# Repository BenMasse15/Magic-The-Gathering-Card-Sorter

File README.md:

TO DO:

- Assembly
- Adapt Motor Code for traditionnal sorting
- Make "Mana Shuffle" option

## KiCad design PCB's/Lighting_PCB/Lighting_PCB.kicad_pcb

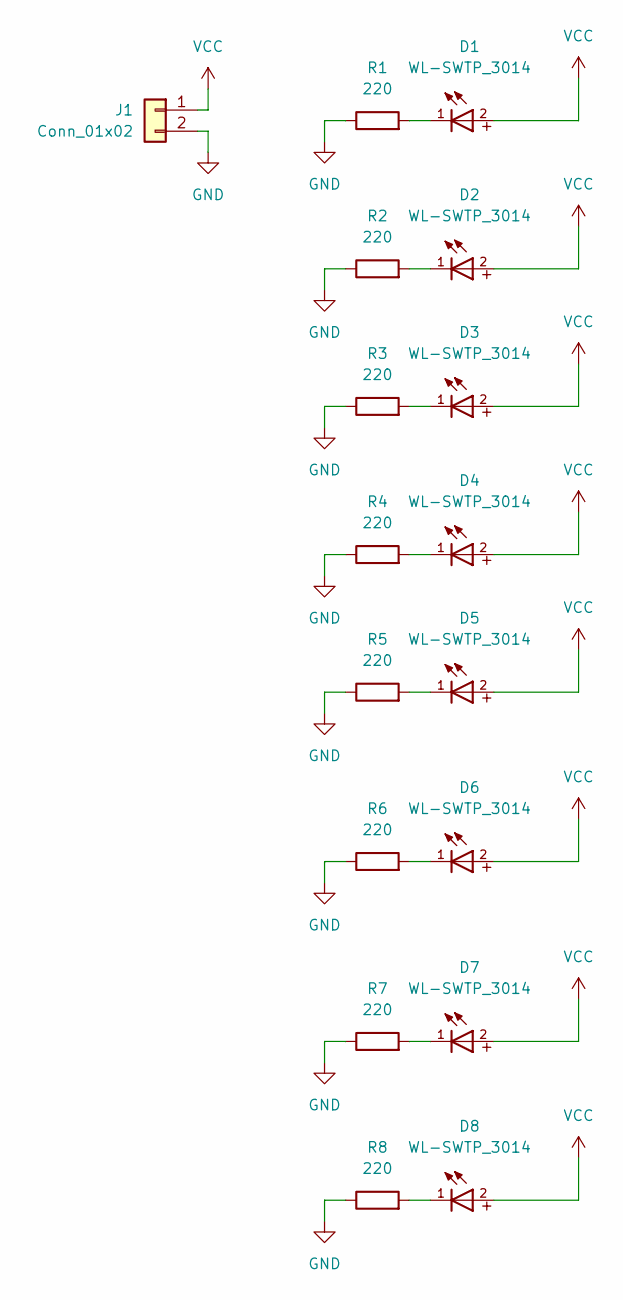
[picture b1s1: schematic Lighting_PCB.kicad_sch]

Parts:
D1, D2, D3, D4, D5, D6, D7, D8: WL-SWTP_3014
J1: Conn_01x02; Molex_KK-254_AE-6410-02A_1x02_P2.54mm_Vertical
R1, R2, R3, R4, R5, R6, R7, R8: 220; R_0805_2012Metric_Pad1.20x1.40mm_HandSolder

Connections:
GND: J1.2, R1.1, R2.1, R3.1, R4.1, R5.1, R6.1, R7.1, R8.1
unnamed: D1.1, R1.2
unnamed: D2.1, R2.2
unnamed: D3.1, R3.2
unnamed: D4.1, R4.2
unnamed: D5.1, R5.2
unnamed: D6.1, R6.2
unnamed: D7.1, R7.2
unnamed: D8.1, R8.2
VCC: D1.2, D2.2, D3.2, D4.2, D5.2, D6.2, D7.2, D8.2, J1.1

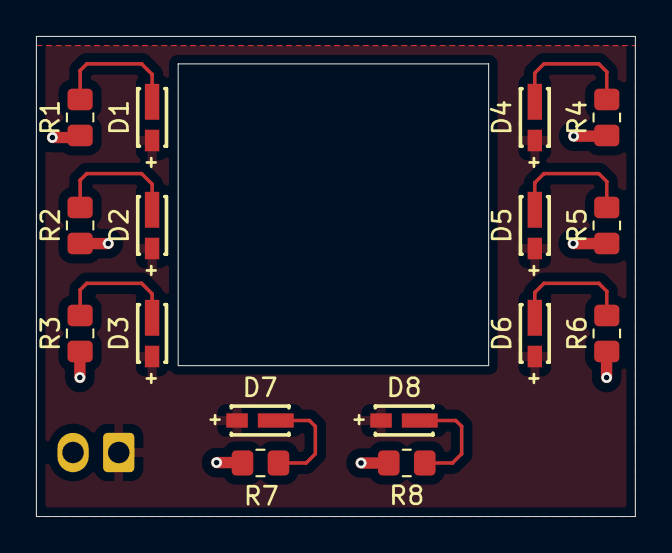
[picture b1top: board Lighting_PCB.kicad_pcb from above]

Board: 2 copper layers, 33.3 x 26.7 mm, 17 parts (1 on the bottom side), 10 nets.

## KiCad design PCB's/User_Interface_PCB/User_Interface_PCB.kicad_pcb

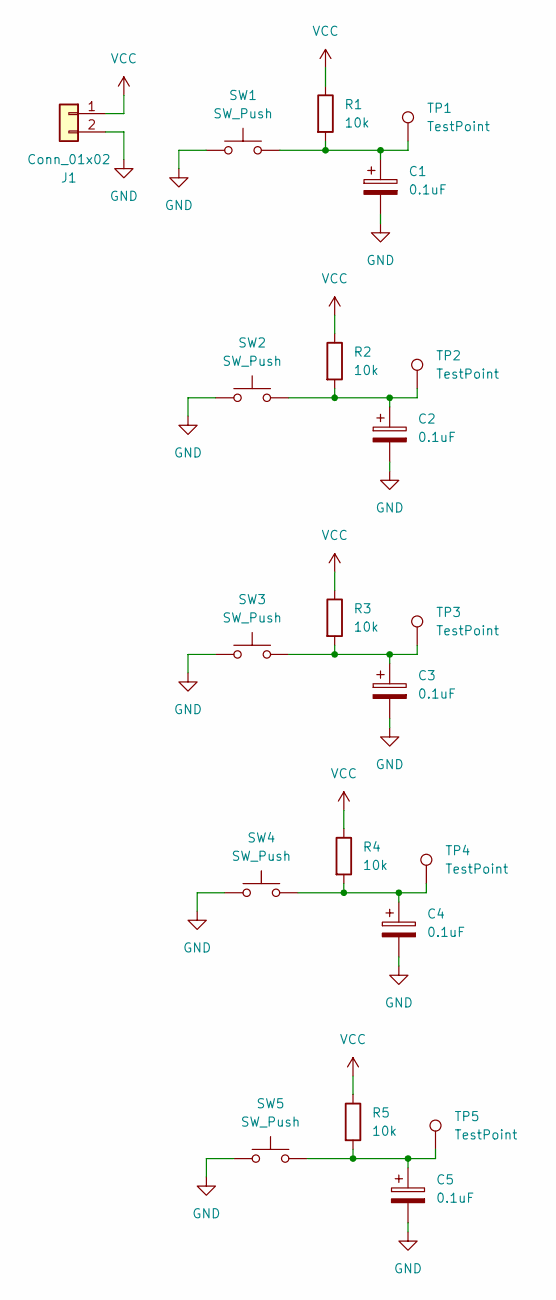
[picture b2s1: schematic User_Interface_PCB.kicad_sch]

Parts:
C1, C2, C3, C4, C5: 0.1uF; C_0805_2012Metric_Pad1.18x1.45mm_HandSolder
J1: Conn_01x02; Molex_KK-254_AE-6410-02A_1x02_P2.54mm_Vertical
R1, R2, R3, R4, R5: 10k; R_0805_2012Metric_Pad1.20x1.40mm_HandSolder
SW1, SW2, SW3, SW4, SW5: SW_Push; SW_MEC_5GTH9
TP1, TP2, TP3, TP4, TP5: TestPoint; TestPoint_Plated_Hole_D2.0mm

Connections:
GND: C1.2, C2.2, C3.2, C4.2, C5.2, J1.2, SW1.1, SW2.1, SW3.1, SW4.1, SW5.1
unnamed: C1.1, R1.2, SW1.2, TP1.1
unnamed: C2.1, R2.2, SW2.2, TP2.1
unnamed: C3.1, R3.2, SW3.2, TP3.1
unnamed: C4.1, R4.2, SW4.2, TP4.1
unnamed: C5.1, R5.2, SW5.2, TP5.1
VCC: J1.1, R1.1, R2.1, R3.1, R4.1, R5.1

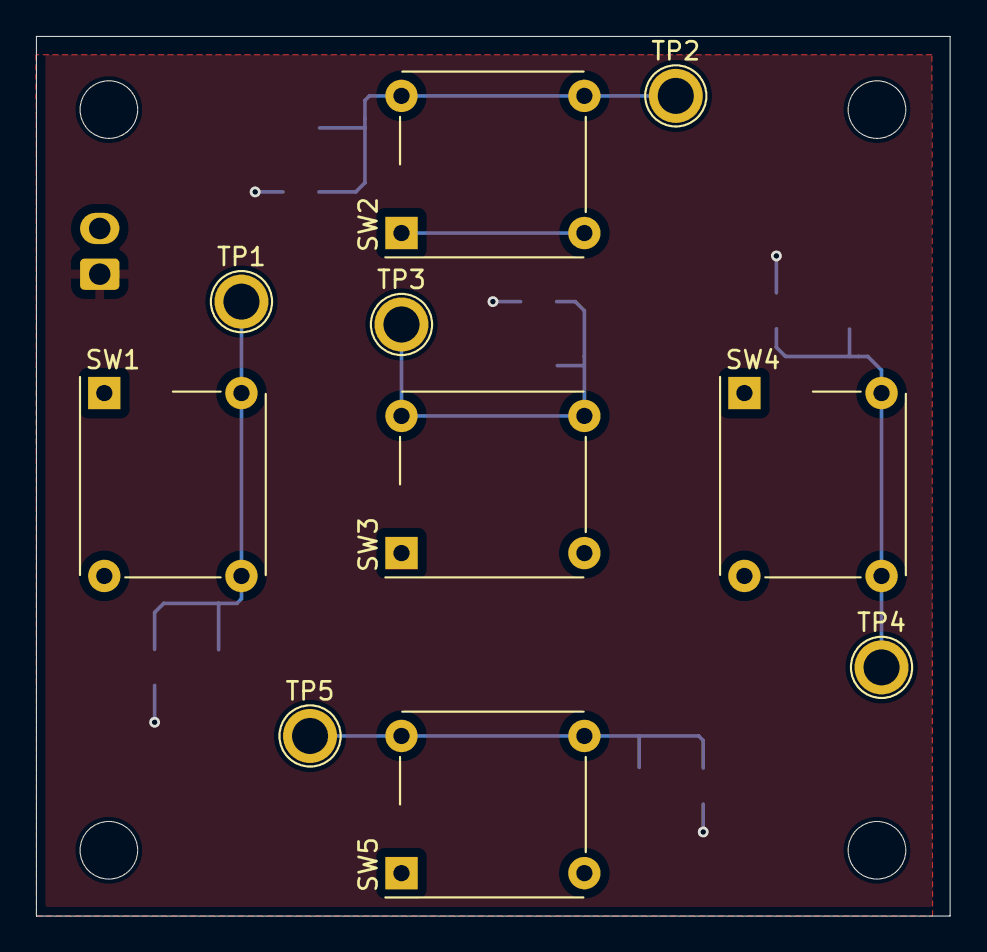
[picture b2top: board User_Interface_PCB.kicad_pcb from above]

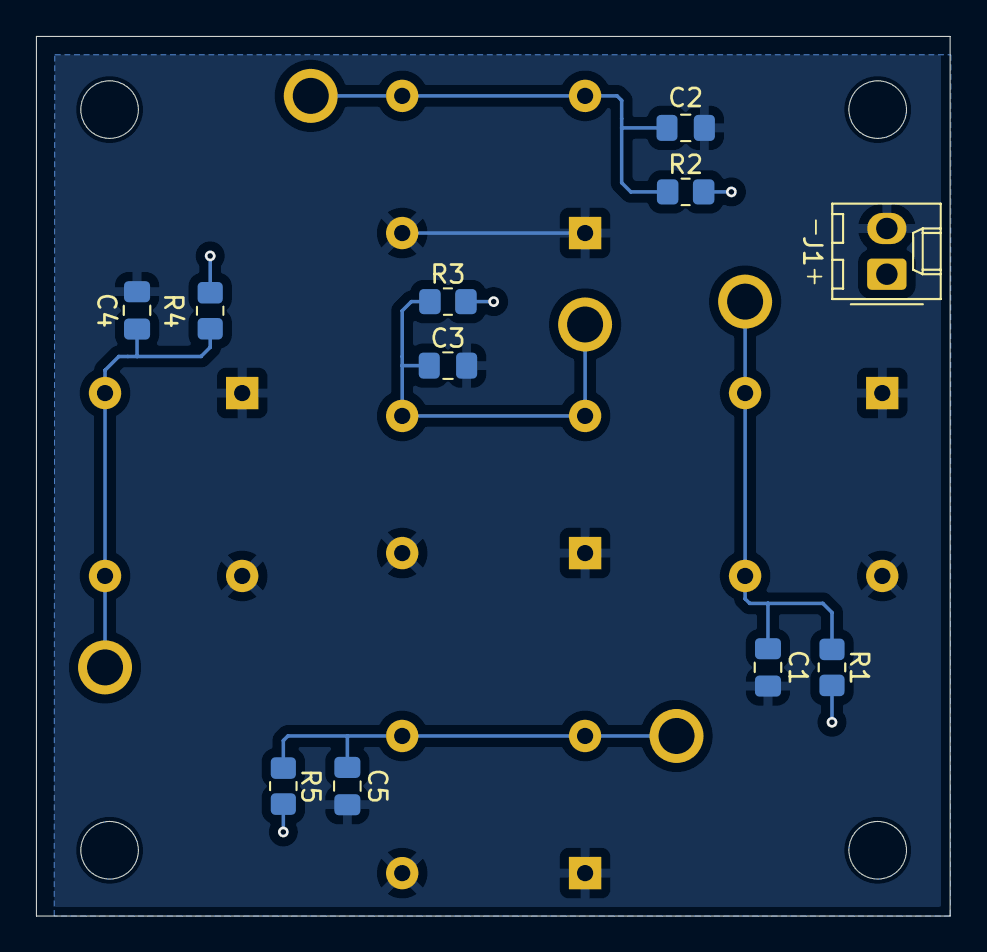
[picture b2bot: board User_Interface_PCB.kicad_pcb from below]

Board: 2 copper layers, 50.8 x 48.9 mm, 21 parts (11 on the bottom side), 7 nets.

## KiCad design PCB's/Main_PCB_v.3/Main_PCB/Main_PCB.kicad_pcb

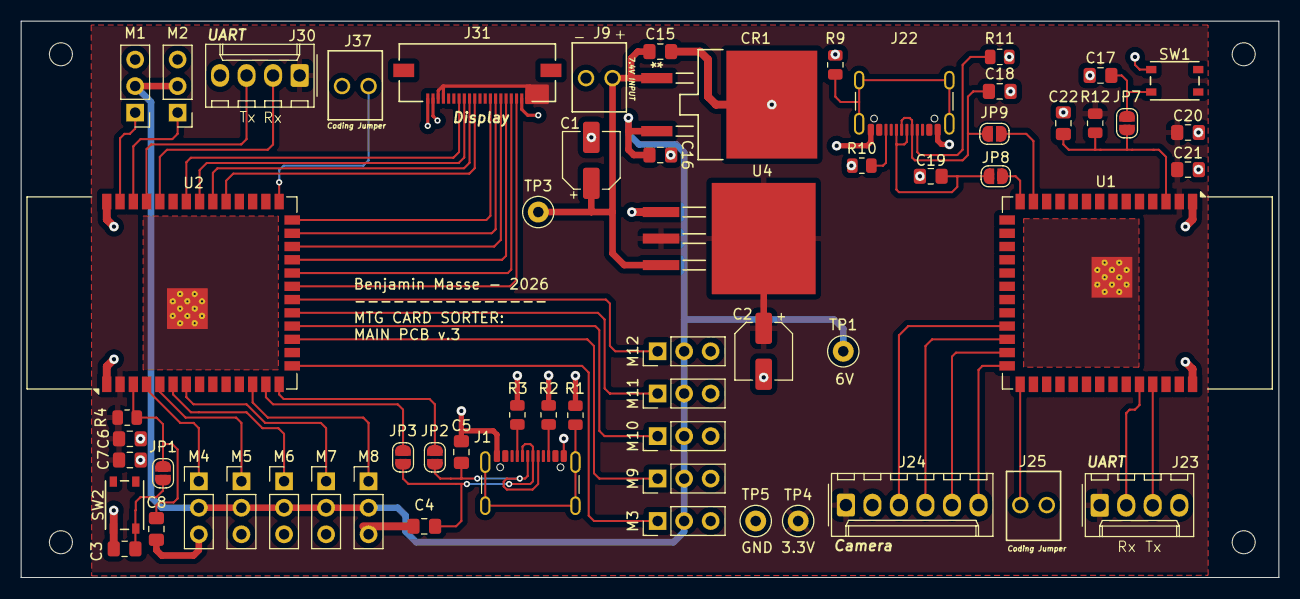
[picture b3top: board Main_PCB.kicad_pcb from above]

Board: 2 copper layers, 120.5 x 53.3 mm, 61 parts (0 on the bottom side), 54 nets.

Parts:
C1, C2: 10uF; CP_Elec_5x5.3
C3, C7, C16, C17, C21: 0.1uF; C_0805_2012Metric_Pad1.18x1.45mm_HandSolder
C4, C5, C18, C19: 47pF; C_0805_2012Metric_Pad1.18x1.45mm_HandSolder
C6, C20: 22uF; C_0805_2012Metric_Pad1.18x1.45mm_HandSolder
C8, C22: 1uF; C_0805_2012Metric_Pad1.18x1.45mm_HandSolder
C15: 0.33uF; C_0805_2012Metric_Pad1.18x1.45mm_HandSolder
CR1: L7806ABD2T-TR; D2PAK_STM
J1, J22: USB_C_Receptacle_USB2.0_14P; USB_C_Receptacle_GCT_USB4105-xx-A_16P_TopMnt_Horizontal
J9: 7.4V Input; CONN_A-6373-02A_MOL
J23, J30: Conn_01x04; Molex_KK-254_AE-6410-04A_1x04_P2.54mm_Vertical
J24: Arducam; Molex_KK-254_AE-6410-06A_1x06_P2.54mm_Vertical
J25, J37: Conn_01x02; CONN_A-6373-02A_MOL
J31: 5051102091 (Display); CONN_5051102091_MOL
JP1, JP2, JP3, JP7, JP8, JP9: SolderJumper_2_Open; SolderJumper-2_P1.3mm_Open_RoundedPad1.0x1.5mm
M1: M1; PinHeader_1x03_P2.54mm_Vertical
M2: M2; PinHeader_1x03_P2.54mm_Vertical
M3: M3; PinHeader_1x03_P2.54mm_Vertical
M4: M4; PinHeader_1x03_P2.54mm_Vertical
M5: M5; PinHeader_1x03_P2.54mm_Vertical
M6: M6; PinHeader_1x03_P2.54mm_Vertical
M7: M7; PinHeader_1x03_P2.54mm_Vertical
M8: M8; PinHeader_1x03_P2.54mm_Vertical
M9: M9; PinHeader_1x03_P2.54mm_Vertical
M10: M10; PinHeader_1x03_P2.54mm_Vertical
M11: M11; PinHeader_1x03_P2.54mm_Vertical
M12: M12; PinHeader_1x03_P2.54mm_Vertical
R1, R9: 1M; R_0805_2012Metric
R2, R3, R10, R11: 5.11k; R_0805_2012Metric
R4, R12: 10k; R_0805_2012Metric
SW1, SW2: PTS815; SW4_PTS815 SJM 250 SMTR LFS_CNK
TP1: 6V; TestPoint_Loop_D2.50mm_Drill1.0mm
TP3: VCC; TestPoint_Loop_D2.50mm_Drill1.0mm
TP4: 3.3V; TestPoint_Loop_D2.50mm_Drill1.0mm
TP5: GND; TestPoint_Loop_D2.50mm_Drill1.0mm
U1, U2: ESP32-S3-WROOM-1
U4: LM1085ISX-3.3/NOPB; KTT3

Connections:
3.3V: C2.1, C6.1, C7.1, C20.1, C21.1, J23.1, J24.1, J30.1, J31.1, J31.17, J31.18, R4.2, R12.2, TP4.1, U1.2 (3V3), U2.2 (3V3), U4.2 (OUTPUT), U4.4 (EPAD)
6V: C16.1, CR1.2 (OUTPUT), M1.2, M2.2, M3.2, M4.2, M5.2, M6.2, M7.2, M8.2, M9.2, M10.2, M11.2, M12.2, TP1.1
/Camera + API/EN1: C22.2, JP7.2 (B), R12.1, U1.3 (EN)
/Screen + Motors/EN2: C8.2, JP1.2 (B), R4.1, U2.3 (EN)
/Screen + Motors/IO1: M1.1, U2.39 (IO1)
/Screen + Motors/IO2: M2.1, U2.38 (IO2)
/Screen + Motors/IO3: M3.1, U2.15 (IO3)
/Screen + Motors/IO4: M4.1, U2.4 (IO4)
/Screen + Motors/IO5: M5.1, U2.5 (IO5)
/Screen + Motors/IO6: M6.1, U2.6 (IO6)
/Screen + Motors/IO7: M7.1, U2.7 (IO7)
/Screen + Motors/IO8: M8.1, U2.12 (IO8)
/Screen + Motors/IO9: M9.1, U2.17 (IO9)
/Screen + Motors/IO10: M10.1, U2.18 (IO10)
/Screen + Motors/IO11: M11.1, U2.19 (IO11)
/Screen + Motors/IO12: M12.1, U2.20 (IO12)
GND: C1.2, C2.2, C3.1, C4.2, C5.2, C6.2, C7.2, C8.1, C15.2, C16.2, C17.1, C18.2, C19.2, C20.2, C21.2, C22.1, CR1.3 (GND), J1.A1 (GND), J1.A12 (GND), J1.B1 (GND), J1.B12 (GND), J9.2, J22.A1 (GND), J22.A12 (GND), J22.B1 (GND), J22.B12 (GND), J23.4, J24.2, J25.2, J30.4, J31.2, J31.19, J31.20, J37.2, M1.3, M2.3, M3.3, M4.3, M5.3, M6.3, M7.3, M8.3, M9.3, M10.3, M11.3, M12.3, R1.2, R2.1, R3.1, R9.2, R10.1, R11.1, SW1.1, SW2.1, TP5.1, U1.1 (GND), U1.40 (GND), U1.41 (GND), U2.1 (GND), U2.40 (GND), U2.41 (GND), U4.1 (ADJ/GND)
unnamed: J1.A5 (CC1), R3.2
unnamed: J1.B5 (CC2), R2.2
unnamed: J1.S1 (SHIELD), R1.1
unnamed: J22.A5 (CC1), R11.2
unnamed: J22.B5 (CC2), R10.2
unnamed: J22.S1 (SHIELD), R9.1
unnamed: J23.2, U1.36 (RXD0)
unnamed: J23.3, U1.37 (TXD0)
unnamed: J24.3, U1.23 (IO21)
unnamed: J24.4, U1.24 (IO47)
unnamed: J24.5, U1.25 (IO48)
unnamed: J24.6, U1.26 (IO45)
unnamed: J25.1, U1.27 (IO0)
unnamed: J30.2, U2.36 (RXD0)
unnamed: J30.3, U2.37 (TXD0)
unnamed: J37.1, U2.27 (IO0)
unnamed: C3.2, JP1.1 (A), SW2.3
unnamed: C5.1, J1.A6 (D+), J1.B6 (D+), JP2.1 (A)
unnamed: JP2.2 (B), U2.14 (USB_D+)
unnamed: C4.1, J1.A7 (D-), J1.B7 (D-), JP3.1 (A)
unnamed: JP3.2 (B), U2.13 (USB_D-)
unnamed: C17.2, JP7.1 (A), SW1.3
unnamed: C19.1, J22.A6 (D+), J22.B6 (D+), JP8.1 (A)
unnamed: JP8.2 (B), U1.14 (USB_D+)
unnamed: C18.1, J22.A7 (D-), J22.B7 (D-), JP9.1 (A)
unnamed: JP9.2 (B), U1.13 (USB_D-)
unnamed: J31.3, U2.21 (IO13)
unnamed: J31.4, U2.22 (IO14)
unnamed: J31.5, U2.23 (IO21)
unnamed: J31.11, U2.31 (IO38)
unnamed: J31.12, U2.32 (IO39)
unnamed: J31.13, U2.33 (IO40)
unnamed: J31.14, U2.34 (IO41)
unnamed: J31.8, U2.26 (IO45)
unnamed: J31.6, U2.24 (IO47)
unnamed: J31.7, U2.25 (IO48)
VCC: C1.1, C15.1, CR1.1 (INPUT), J9.1, TP3.1, U4.3 (INPUT)

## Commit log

2026-04-12 Official Organised Repository for my Personal Project
2026-04-12 Testing Branch
2026-04-12 Branch Testing
2026-04-12 3d models of the slides, camera adapter and board adapter
2026-04-12 Add TO DO section to README
2026-04-16 updated motors code to add motor control
2026-04-17 Motor now works 180 degrees instead of 90 and added basic hello world screen config for reference tmr
2026-04-17 Added basic screen config to the code
2026-04-19 added screen showing qty and a reset button
2026-04-19 working with new further away camera
2026-04-21 sending all local for presentation
2026-04-21 Function no wifi
2026-04-22 Lighting and user interface pcb's
2026-05-08 added new code to test if Scryfall works on school WiFi
2026-05-08 TCG SORTER REMODEL
2026-05-11 testing
2026-05-11 servos dont work
2026-05-11 servos still fucked
2026-05-11 holy motors work
2026-05-11 added camera lib without examples
2026-05-11 if needed when on a new pc
2026-05-11 working on motors
2026-05-11 servos kinda working
2026-05-12 lands done in testing, creature needs adjusment
2026-05-12 presentation version
2026-05-19 updated codes
2026-05-19 version presentation
2026-05-22 3D models updated
2026-05-26 bilan final complet
2026-06-01 présentation jury
